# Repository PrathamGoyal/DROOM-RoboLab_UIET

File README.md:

# SmartParking_IPD-RoboLab_UIET
All the work that will be done by me in this project under Robotics lab UIET.

My task is to learn eagle PCB designing software and make a PCB design of my IPD project before 15th July. Following is my timeline for the project. 
1. Till 5th July I will learn about all the basics required for making PCB design using Eagle.
2. Till 10th July I will be practicing on sample projects which will be uploaded on my Github.
3. After I have practiced enough on sample projects then I will work on making PCB design of my IPD project. Which will be finished by 15th July.

Finished as per above given timeline.
Work done in Circuit designing was satisfactory according to Seniors.

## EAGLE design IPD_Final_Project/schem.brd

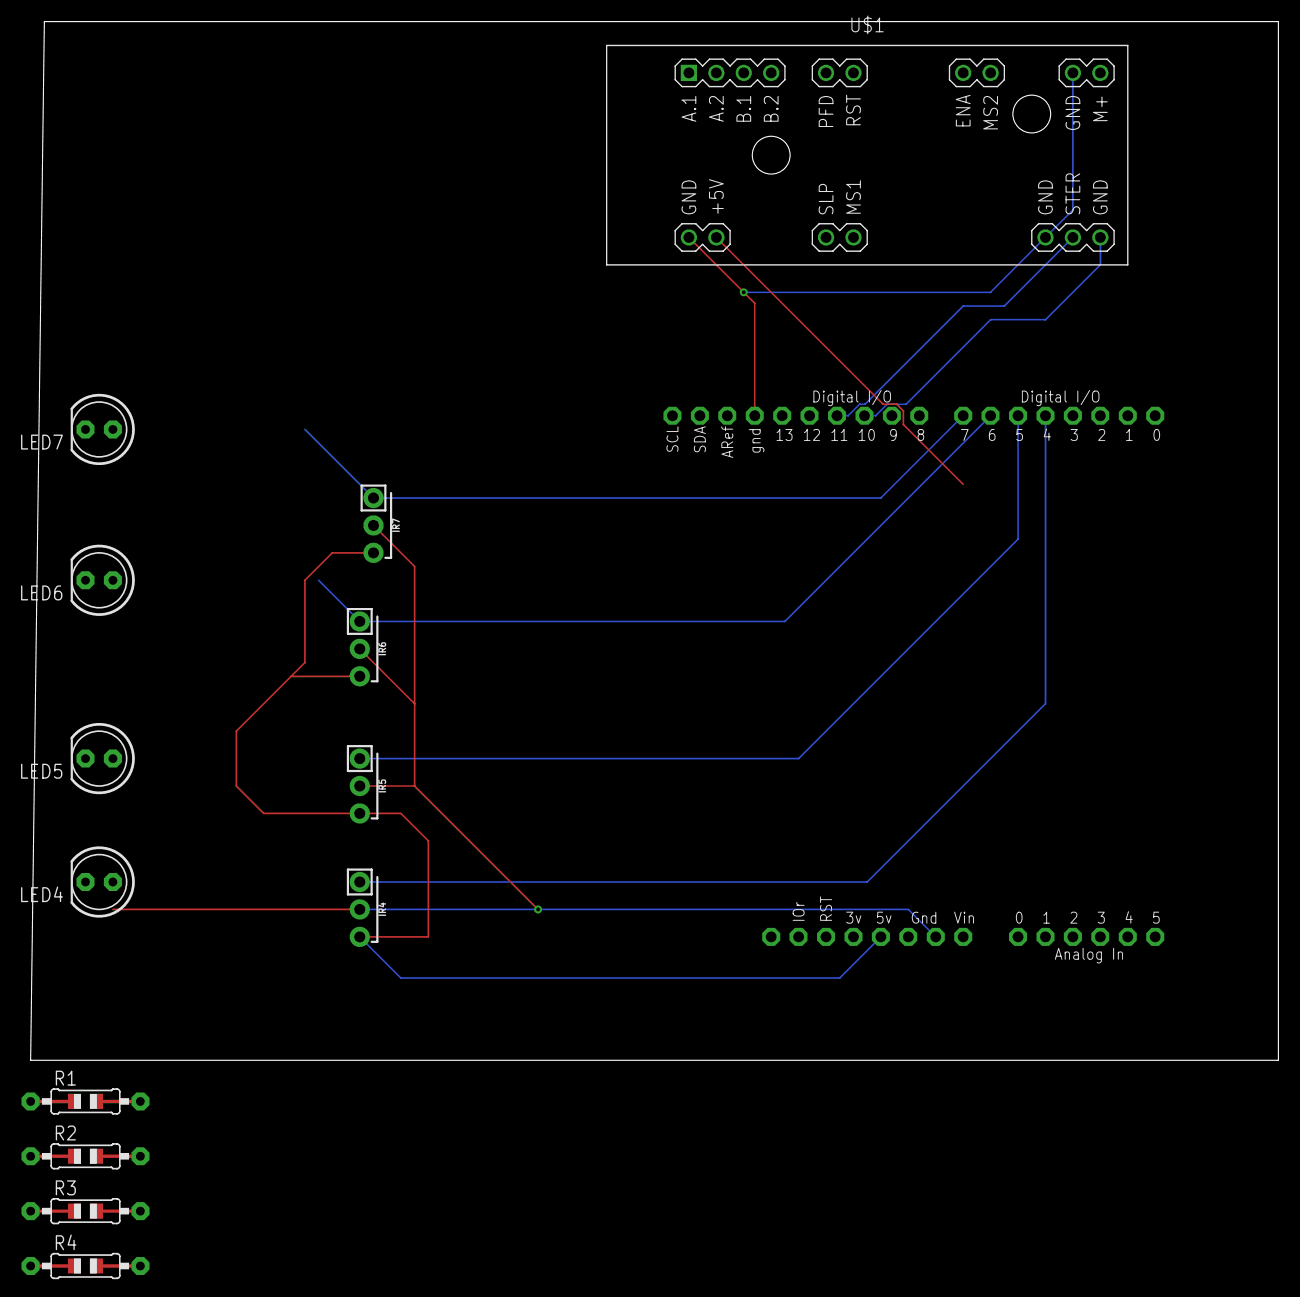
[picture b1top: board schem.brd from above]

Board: 2 copper layers, 115.5 x 96.2 mm, 14 parts (0 on the bottom side), 14 nets.

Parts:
IR4, IR5, IR6, IR7: BRM-2508RA; BRM-2508
LED4, LED5, LED6, LED7: LED5MM
R1, R2, R3, R4: 0805-THM
U1: ARDUINOR3-BPLACE
U$1: STEPPER-MOTOR-EASY-DRIVER

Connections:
GND: U1.GND, U$1.JP1.1, U$1.JP2.1, U$1.JP4.2
unnamed: LED6.A, R2.1
unnamed: U1.D10, U$1.JP2.3
unnamed: U1.D11, U$1.JP2.2
unnamed: LED5.A, R3.1
unnamed: LED4.A, R4.1
unnamed: LED7.A, R1.1
unnamed: IR4.3, IR5.3, IR6.3, IR7.3, U1.5V
unnamed: IR4.1, R4.2, U1.D4
unnamed: IR4.2, IR5.2, IR6.2, IR7.2, LED4.K, LED5.K, LED6.K, LED7.K, U1.GND1
unnamed: IR5.1, R3.2, U1.D5
unnamed: IR6.1, R2.2, U1.D6
unnamed: IR7.1, R1.2, U1.D7
V_IN: U1.VIN, U$1.JP4.1

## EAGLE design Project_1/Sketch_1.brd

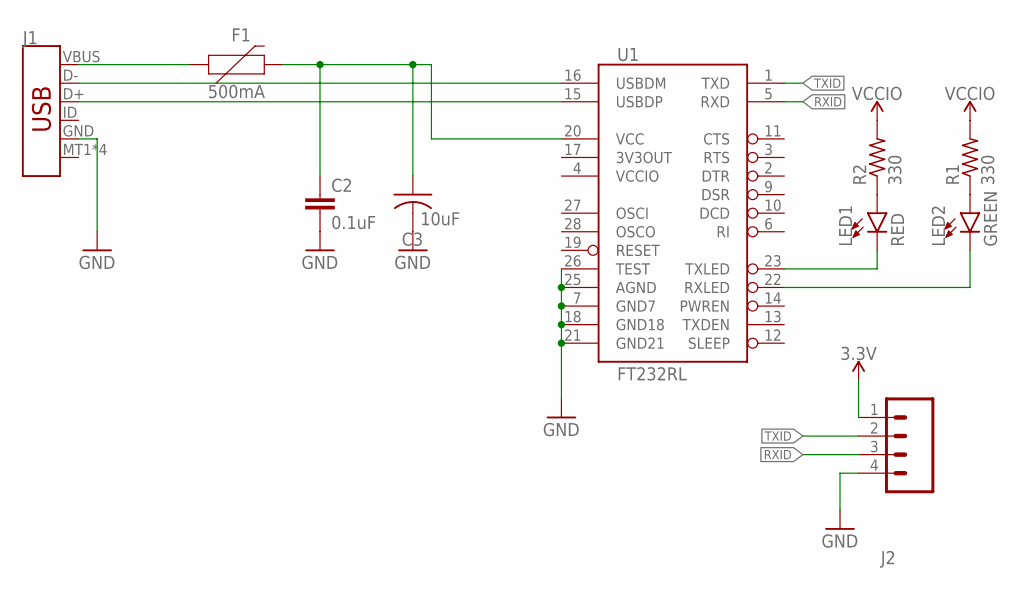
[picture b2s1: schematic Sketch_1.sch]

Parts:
C2: 0.1uF; C1206K
C3: 10uF; C1206K
F1: 500mA; 0805
J1: USB_MICRO-B_SMT; USB-MICROB
J2: M04; 04P
LED1: RED; LED-1206
LED2: GREEN; LED-1206
R1, R2: 330; R1206
U1: FT232RL; SSOP28DB

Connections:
GND: C2.2, C3.2, J1.GND, J2.4, U1.7 (GND7), U1.18 (GND18), U1.21 (GND21), U1.25 (AGND), U1.26 (TEST)
unnamed: F1.1, J1.VBUS
unnamed: C2.1, C3.1, F1.2, U1.20 (VCC)
unnamed: J1.D-, U1.16 (USBDM)
unnamed: J1.D+, U1.15 (USBDP)
unnamed: LED2.A, R1.1
unnamed: LED1.A, R2.1
unnamed: LED1.C, U1.23 (TXLED)
unnamed: LED2.C, U1.22 (RXLED)
RXID: J2.3, U1.5 (RXD)
TXID: J2.2, U1.1 (TXD)
VCC: J2.1
VCCIO: R1.2, R2.2, U1.4 (VCCIO)

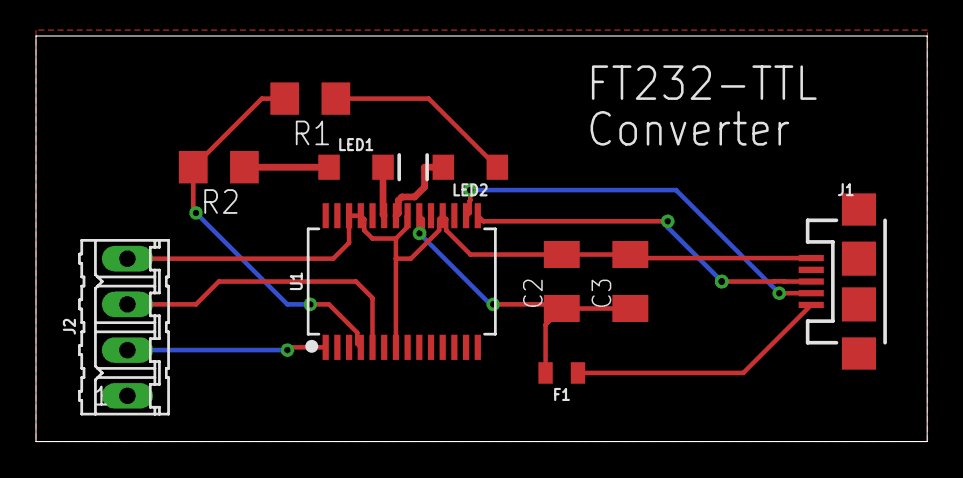
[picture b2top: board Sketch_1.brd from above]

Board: 2 copper layers, 49.5 x 22.5 mm, 10 parts (0 on the bottom side), 12 nets.

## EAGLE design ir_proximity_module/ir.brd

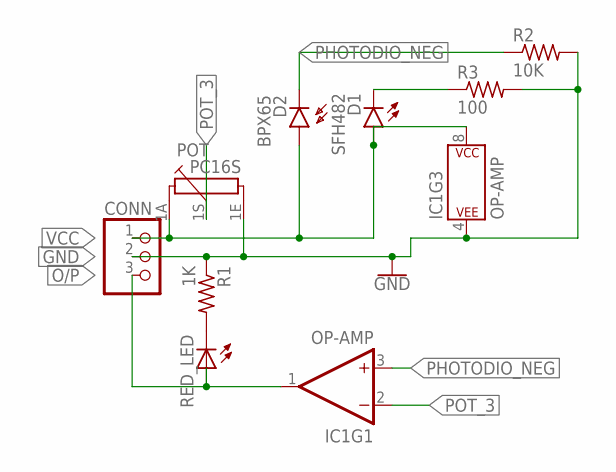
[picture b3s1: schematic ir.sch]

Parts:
CONN: PINHD-1X3; 1X03
D1: SFH482
D2: BPX65
IC1: OP-AMP; DIP08
POT: PC16S
R1: 1K; 0805-THM
R2: 10K; 0805-THM
R3: 100; 0805-THM
RED_LED: LED3MM

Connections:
GND: CONN.2, IC1.4 (P$V-), POT.1E, R1.1, R2.2, R3.2
unnamed: R1.2, RED_LED.K (C)
unnamed: D1.K (C), R3.1
O/P: CONN.3, IC1.1 (OUT), RED_LED.A
PHOTODIO_NEG: D2.K (C), IC1.3 (+IN), R2.1
POT_3: IC1.2 (-IN), POT.1S
VCC: CONN.1, D1.A, D2.A, IC1.8 (P$V+), POT.1A

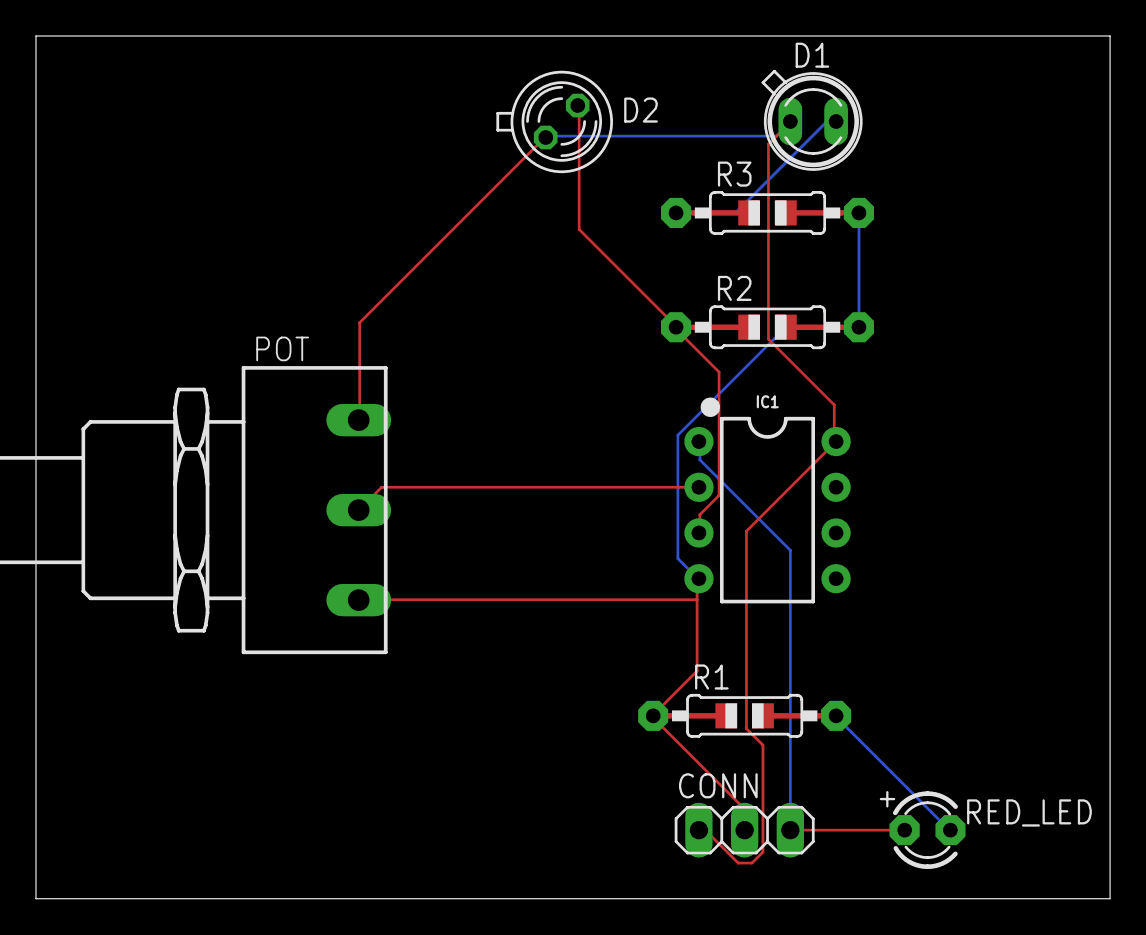
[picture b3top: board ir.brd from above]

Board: 2 copper layers, 59.7 x 47.9 mm, 9 parts (0 on the bottom side), 7 nets.

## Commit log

2019-06-30 Update README.md
    Added Timeline of the project.
2019-07-02 Update README.md
    Made some changes as suggested.
2019-07-06 Add files via upload
    First Project using Eagle
2019-07-20 Add files via upload
    Added files for final project
2019-10-06 Added Closing notes in Readme
    The project is finished and the end result has been added in the Readme file.

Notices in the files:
parts and their libraries:
SparkFun-Sensors: Licensing: Creative Commons ShareAlike 4.0 International - https://creativecommons.org/licenses/by-sa/4.0
diy-modules: Released under the Creative Commons Attribution 4.0 International License: http://creativecommons.org/licenses/by/4.0
